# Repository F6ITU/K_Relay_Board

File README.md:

# K_Relay_Board
LA2NI's OpenHPSDR 4 ways HF relay board (Kicad Version)

OpenHPSDR P.A. Antenna switch board by LA2NI (Munin 400/Aries system)

This relay board is part of a set consisting of a 400 W LDMos based RF power amplifier (Munin 400), 
a medium power (600 or 1500 W) Zolotarev low pass filter, an Automatic Antenna Tuner (ATU) nickname « Aries » 
and a 4 port antenna switch (this project).

All these developments are the work and intellectual property of Kjell Karlsen LA2NI and Laurence Barker G8NJJ.

This original work can be downloaded from 

https://github.com/LA2NI/

https://github.com/laurencebarker

The Antenna switch board ensures the switching between 4 antennas under the control of the Aries ATU board. Each of the connected antennas
have a profile stored in the memory of the Aries MCU module. This way, switching from an antenna to the other don't need a new 
tuning solution if the couple "frequency/antenna" has already been defined. 

For more information, please refer to the Aries documentation (in the G8NJJ github repository)

This board was originally developed in September 2021 by Kjell LA2NI , with UltiBoard EDA. This repository is a « bug for bug » clone of the original Protection Board using the Opensource 
Kicad EDA. All these KiCad files are, consequently, the intellectual property of Kjell LA2NI.

This portage (convertion/translation) is placed under the CERN Open source/ Open hardware Licence.

Kicad is an Opensource EDA software maintained by the European Reseach Center CERN (Conseil européen pour la recherche nucléaire)

The original work is protected by the TAPR Open Hardware licence

# Work is RTM
Design is considered as finished, no prototype have been assembled so far. This project is RTM without waranty

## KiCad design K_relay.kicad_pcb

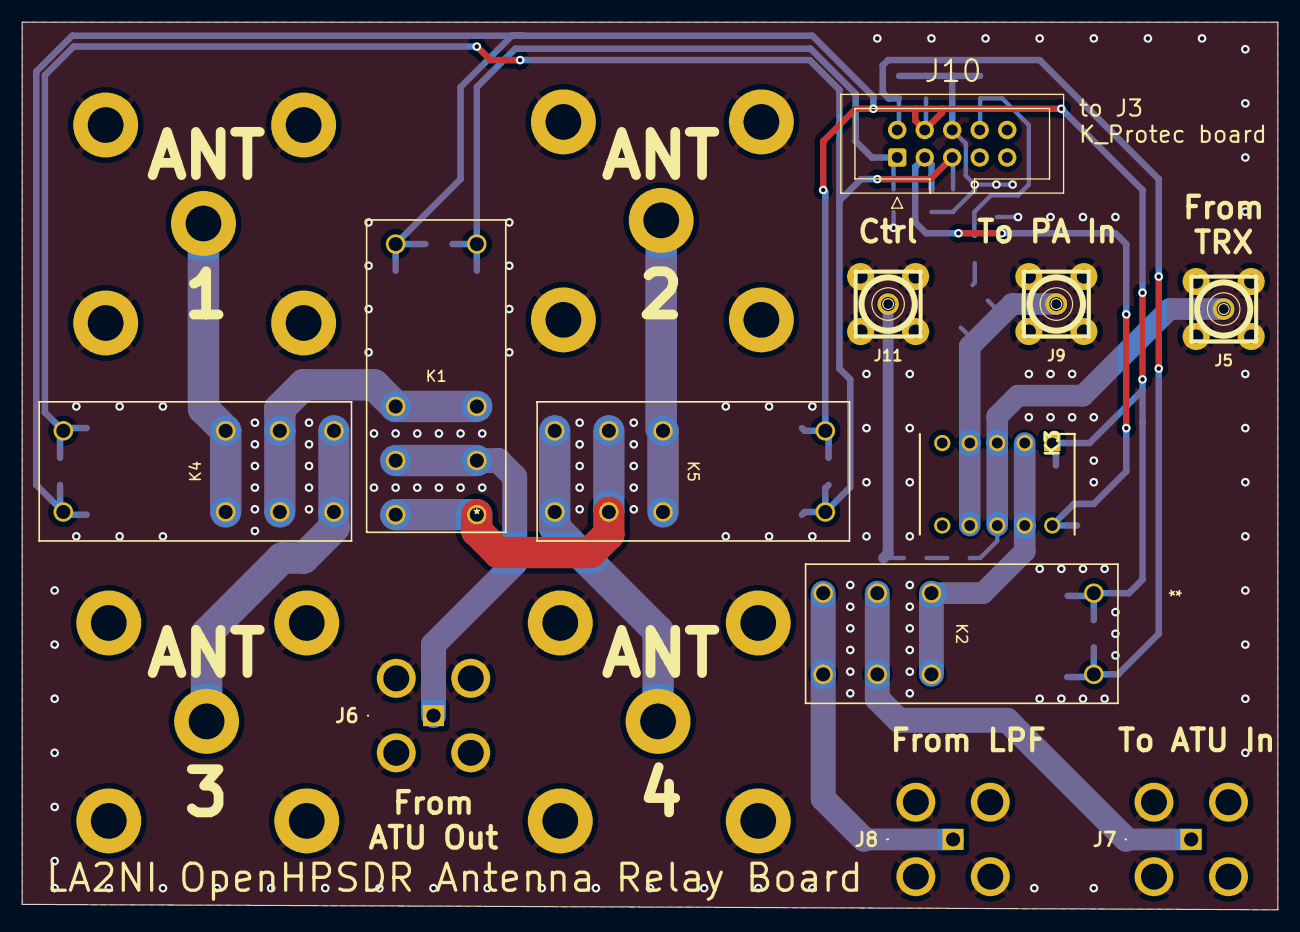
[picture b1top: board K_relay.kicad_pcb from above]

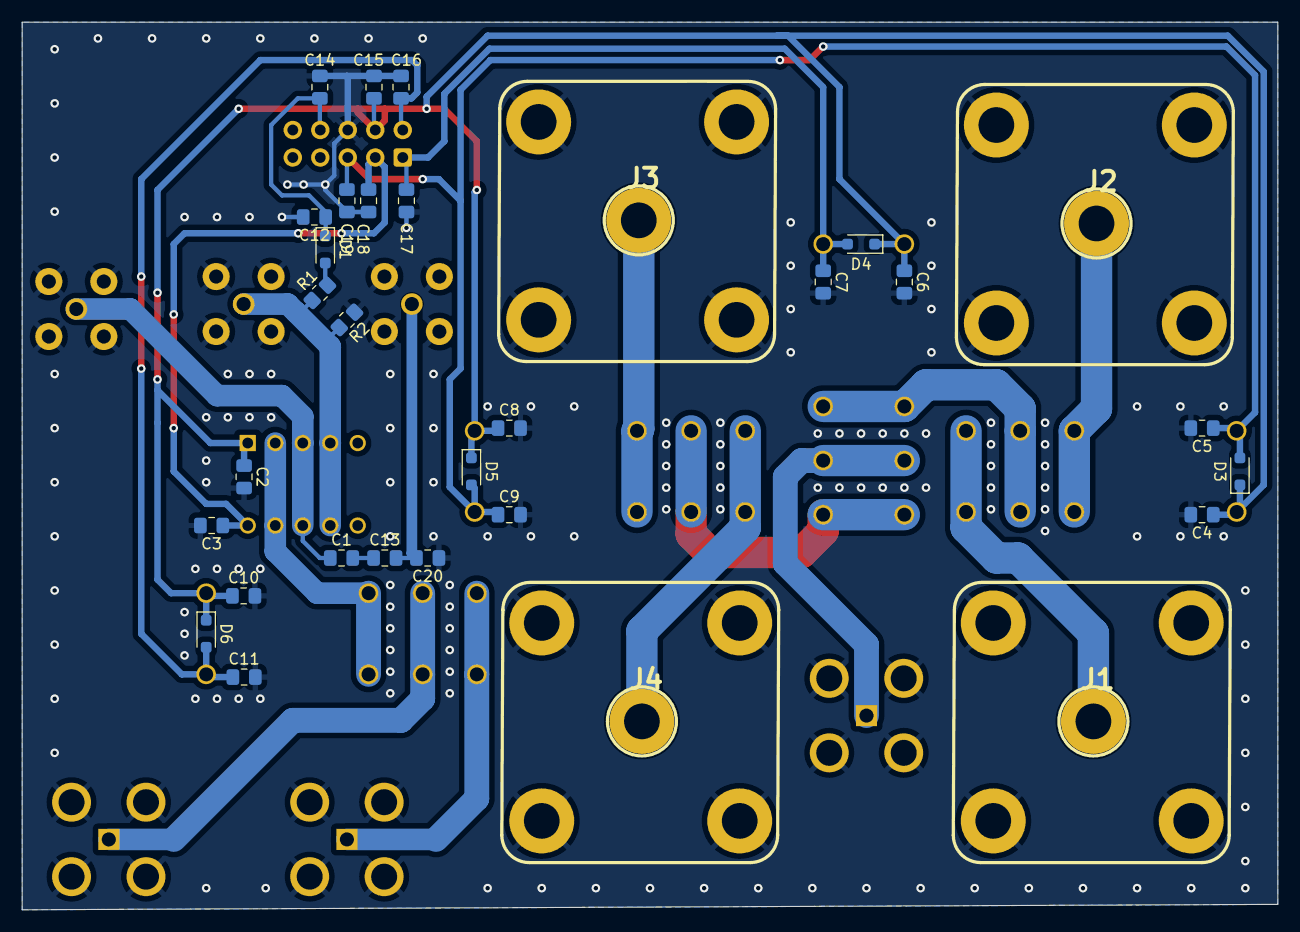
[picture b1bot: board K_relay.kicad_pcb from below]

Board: 2 copper layers, 116.0 x 82.0 mm, 43 parts (31 on the bottom side), 22 nets.

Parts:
C1, C13: 22p; C_0805_2012Metric_Pad1.18x1.45mm_HandSolder
C2, C5, C7, C9, C11: 10n; C_0805_2012Metric_Pad1.18x1.45mm_HandSolder
C3, C4, C6, C8, C10, C12, C14, C15, C16, C17, C18, C19: 100n; C_0805_2012Metric_Pad1.18x1.45mm_HandSolder
C20: 100p; C_0805_2012Metric_Pad1.18x1.45mm_HandSolder
D1: BAS16J; D_SOD-323_HandSoldering
D3, D4, D5, D6: D_Small; D_SOD-323_HandSoldering
J1: ANT3; Coaxial_N_Flange
J2: ANT1; Coaxial_N_Flange
J3: ANT2; Coaxial_N_Flange
J4: ANT4; Coaxial_N_Flange
J5: TRX From SDR; SMA_PINS
J6: FROM ATU OUT; BNC_Amphenol_031532951RFX
J7: TO ATU IN; BNC_Amphenol_031532951RFX
J8: FROM LPF; BNC_Amphenol_031532951RFX
J9: To PA input; SMA_PINS
J10: Con_IDC; IDC-Header_2x05_P2.54mm_Vertical
J11: To CTL; SMA_PINS
K1, K2, K4, K5: TRA2 L-12VDC-S-Z; RELAY_G2R-1-E AC12
K3: TQ2-12V; DIPS762W80P254L1400H530Q10N
R1: 33k; R_0805_2012Metric_Pad1.20x1.40mm_HandSolder
R2: 5K6; R_0805_2012Metric_Pad1.20x1.40mm_HandSolder

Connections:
+12V: C2.1, C4.1, C6.1, C8.1, C10.1, C15.1, D3.1 (K), D4.1 (K), D5.1 (K), D6.1 (K), J10.4, K1.1, K2.1, K3.1, K4.1, K5.1
GND: C2.2, C3.2, C4.2, C5.2, C6.2, C7.2, C8.2, C9.2, C10.2, C11.2, C12.2, C14.2, C15.2, C16.2, C17.2, C18.2, C19.2, C20.1, J1.2 (Ext), J2.2 (Ext), J3.2 (Ext), J4.2 (Ext), J5.2 (Ext), J6.2 (Ext), J7.2 (Ext), J8.2 (Ext), J9.2 (Ext), J10.6, J11.2 (Ext), R2.1
K1: C7.1, C17.1, D4.2 (A), J10.1, K1.8
K2: C11.1, C16.1, D6.2 (A), J10.2, K2.8
K3: C3.1, C18.1, J10.3, K3.10
K5-4: C5.1, C9.1, C19.1, D3.2 (A), D5.2 (A), J10.5, K4.8, K5.8
unnamed: C1.2, C13.1
unnamed: D1.2 (A), R1.2
unnamed: J1.1 (In), K4.4, K4.5
unnamed: J2.1 (In), K4.2, K4.7
unnamed: J3.1 (In), K5.2, K5.7
unnamed: J4.1 (In), K5.4, K5.5
unnamed: C1.1, J5.1 (In), K3.3, K3.8
unnamed: J6.1 (In), K1.3, K1.6
unnamed: J7.1 (In), K2.3, K2.6
unnamed: J8.1 (In), K2.4, K2.5
unnamed: J9.1 (In), K3.4, K3.7, R1.1, R2.2
unnamed: C13.2, C20.2, J11.1 (In)
unnamed: K1.2, K1.7, K4.3, K4.6
unnamed: K1.4, K1.5, K5.3, K5.6
unnamed: K2.2, K2.7, K3.2, K3.9
PWR_DC: C12.1, C14.1, D1.1 (K), J10.8

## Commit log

2023-05-13 first commit, new README
2023-05-13 schematic partialy done
2023-05-13 schematic completed
2023-05-14 schematic completed, footprint & 3D shapes ok
2023-05-14 traces completed, silk need some cleaning
2023-05-14 minor mods in routing, silk cleaned, ibom and gerber ok
2023-05-14 new README
